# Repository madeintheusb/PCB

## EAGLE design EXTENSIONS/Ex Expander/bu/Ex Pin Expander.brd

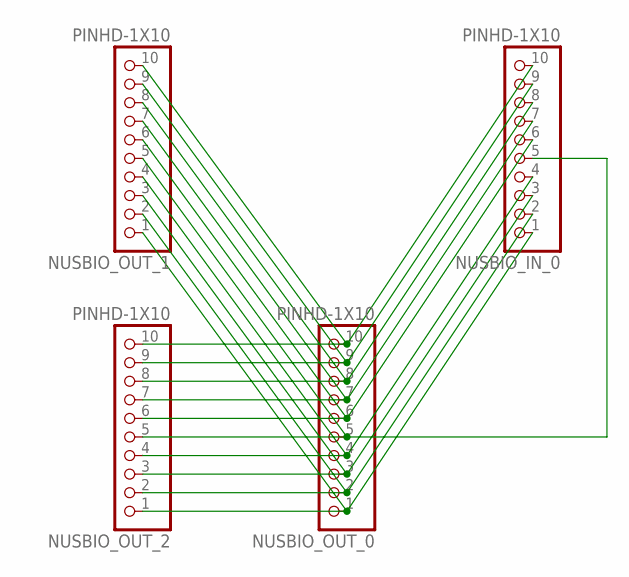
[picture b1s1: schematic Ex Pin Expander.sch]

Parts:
NUSBIO_IN_0: PINHD-1X10; 1X10-BIG
NUSBIO_OUT_0, NUSBIO_OUT_1, NUSBIO_OUT_2: PINHD-1X10; 1X10-BIG

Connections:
unnamed: NUSBIO_IN_0.10, NUSBIO_OUT_0.10, NUSBIO_OUT_1.10, NUSBIO_OUT_2.10
unnamed: NUSBIO_IN_0.9, NUSBIO_OUT_0.9, NUSBIO_OUT_1.9, NUSBIO_OUT_2.9
unnamed: NUSBIO_IN_0.8, NUSBIO_OUT_0.8, NUSBIO_OUT_1.8, NUSBIO_OUT_2.8
unnamed: NUSBIO_IN_0.7, NUSBIO_OUT_0.7, NUSBIO_OUT_1.7, NUSBIO_OUT_2.7
unnamed: NUSBIO_IN_0.6, NUSBIO_OUT_0.6, NUSBIO_OUT_1.6, NUSBIO_OUT_2.6
unnamed: NUSBIO_IN_0.5, NUSBIO_OUT_0.5, NUSBIO_OUT_1.5, NUSBIO_OUT_2.5
unnamed: NUSBIO_IN_0.4, NUSBIO_OUT_0.4, NUSBIO_OUT_1.4, NUSBIO_OUT_2.4
unnamed: NUSBIO_IN_0.3, NUSBIO_OUT_0.3, NUSBIO_OUT_1.3, NUSBIO_OUT_2.3
unnamed: NUSBIO_IN_0.2, NUSBIO_OUT_0.2, NUSBIO_OUT_1.2, NUSBIO_OUT_2.2
unnamed: NUSBIO_IN_0.1, NUSBIO_OUT_0.1, NUSBIO_OUT_1.1, NUSBIO_OUT_2.1

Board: 2 copper layers, 4 parts (0 on the bottom side), 10 nets, no tracks yet.

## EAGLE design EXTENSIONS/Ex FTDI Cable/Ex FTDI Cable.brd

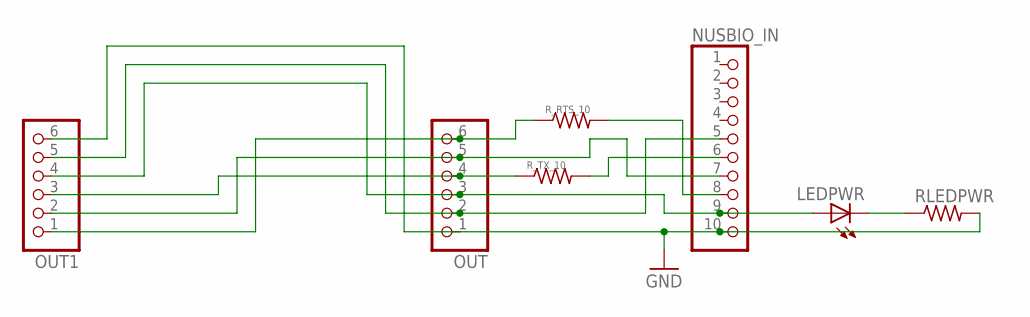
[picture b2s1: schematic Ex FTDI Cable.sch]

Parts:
LEDPWR: LEDCHIPLED_0805; CHIPLED_0805
NUSBIO_IN: PINHD-1X10; 1X10-BIG
OUT, OUT1: PINHD-1X6; 1X06
RLEDPWR: R-US_R0805; R0805
R_RTS_10: R-US_R0805; R0805
R_TX_10: R-US_R0805; R0805

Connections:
GND: NUSBIO_IN.10, OUT.1, OUT1.6, RLEDPWR.2
unnamed: NUSBIO_IN.5, OUT.2, OUT1.5
unnamed: NUSBIO_IN.6, R_TX_10.2
unnamed: NUSBIO_IN.7, OUT.5, OUT1.2
unnamed: NUSBIO_IN.8, R_RTS_10.2
unnamed: OUT.4, OUT1.3, R_TX_10.1
unnamed: OUT.6, OUT1.1, R_RTS_10.1
unnamed: LEDPWR.C, RLEDPWR.1
unnamed: LEDPWR.A, NUSBIO_IN.9, OUT.3, OUT1.4

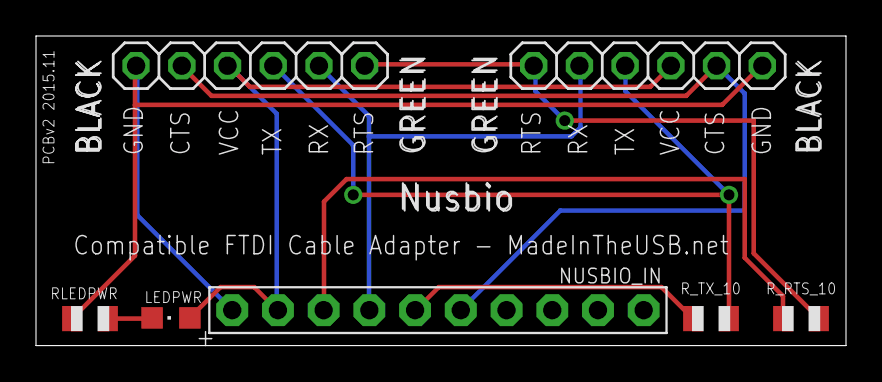
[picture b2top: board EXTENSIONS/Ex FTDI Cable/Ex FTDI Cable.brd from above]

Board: 2 copper layers, 45.0 x 17.2 mm, 7 parts (0 on the bottom side), 9 nets.

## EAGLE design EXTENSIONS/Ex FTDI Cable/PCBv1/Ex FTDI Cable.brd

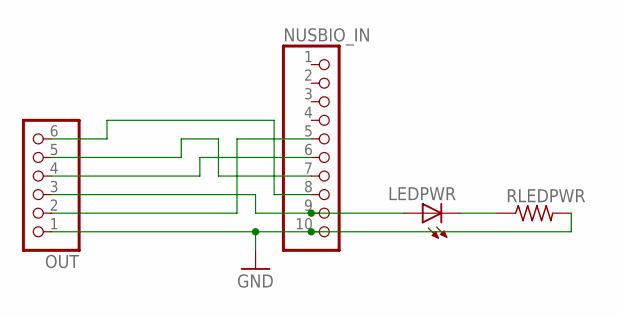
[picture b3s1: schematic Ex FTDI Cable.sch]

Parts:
LEDPWR: LEDCHIPLED_0805; CHIPLED_0805
NUSBIO_IN: PINHD-1X10; 1X10-BIG
OUT: PINHD-1X6; 1X06
RLEDPWR: R-US_R0805; R0805

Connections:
GND: NUSBIO_IN.10, OUT.1, RLEDPWR.2
unnamed: NUSBIO_IN.5, OUT.2
unnamed: NUSBIO_IN.6, OUT.4
unnamed: NUSBIO_IN.7, OUT.5
unnamed: NUSBIO_IN.8, OUT.6
unnamed: LEDPWR.C, RLEDPWR.1
unnamed: LEDPWR.A, NUSBIO_IN.9, OUT.3

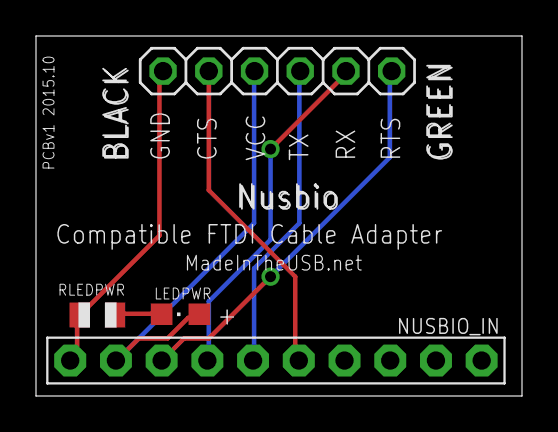
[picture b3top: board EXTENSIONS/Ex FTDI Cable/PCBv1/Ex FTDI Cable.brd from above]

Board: 2 copper layers, 27.0 x 20.0 mm, 4 parts (0 on the bottom side), 7 nets.
